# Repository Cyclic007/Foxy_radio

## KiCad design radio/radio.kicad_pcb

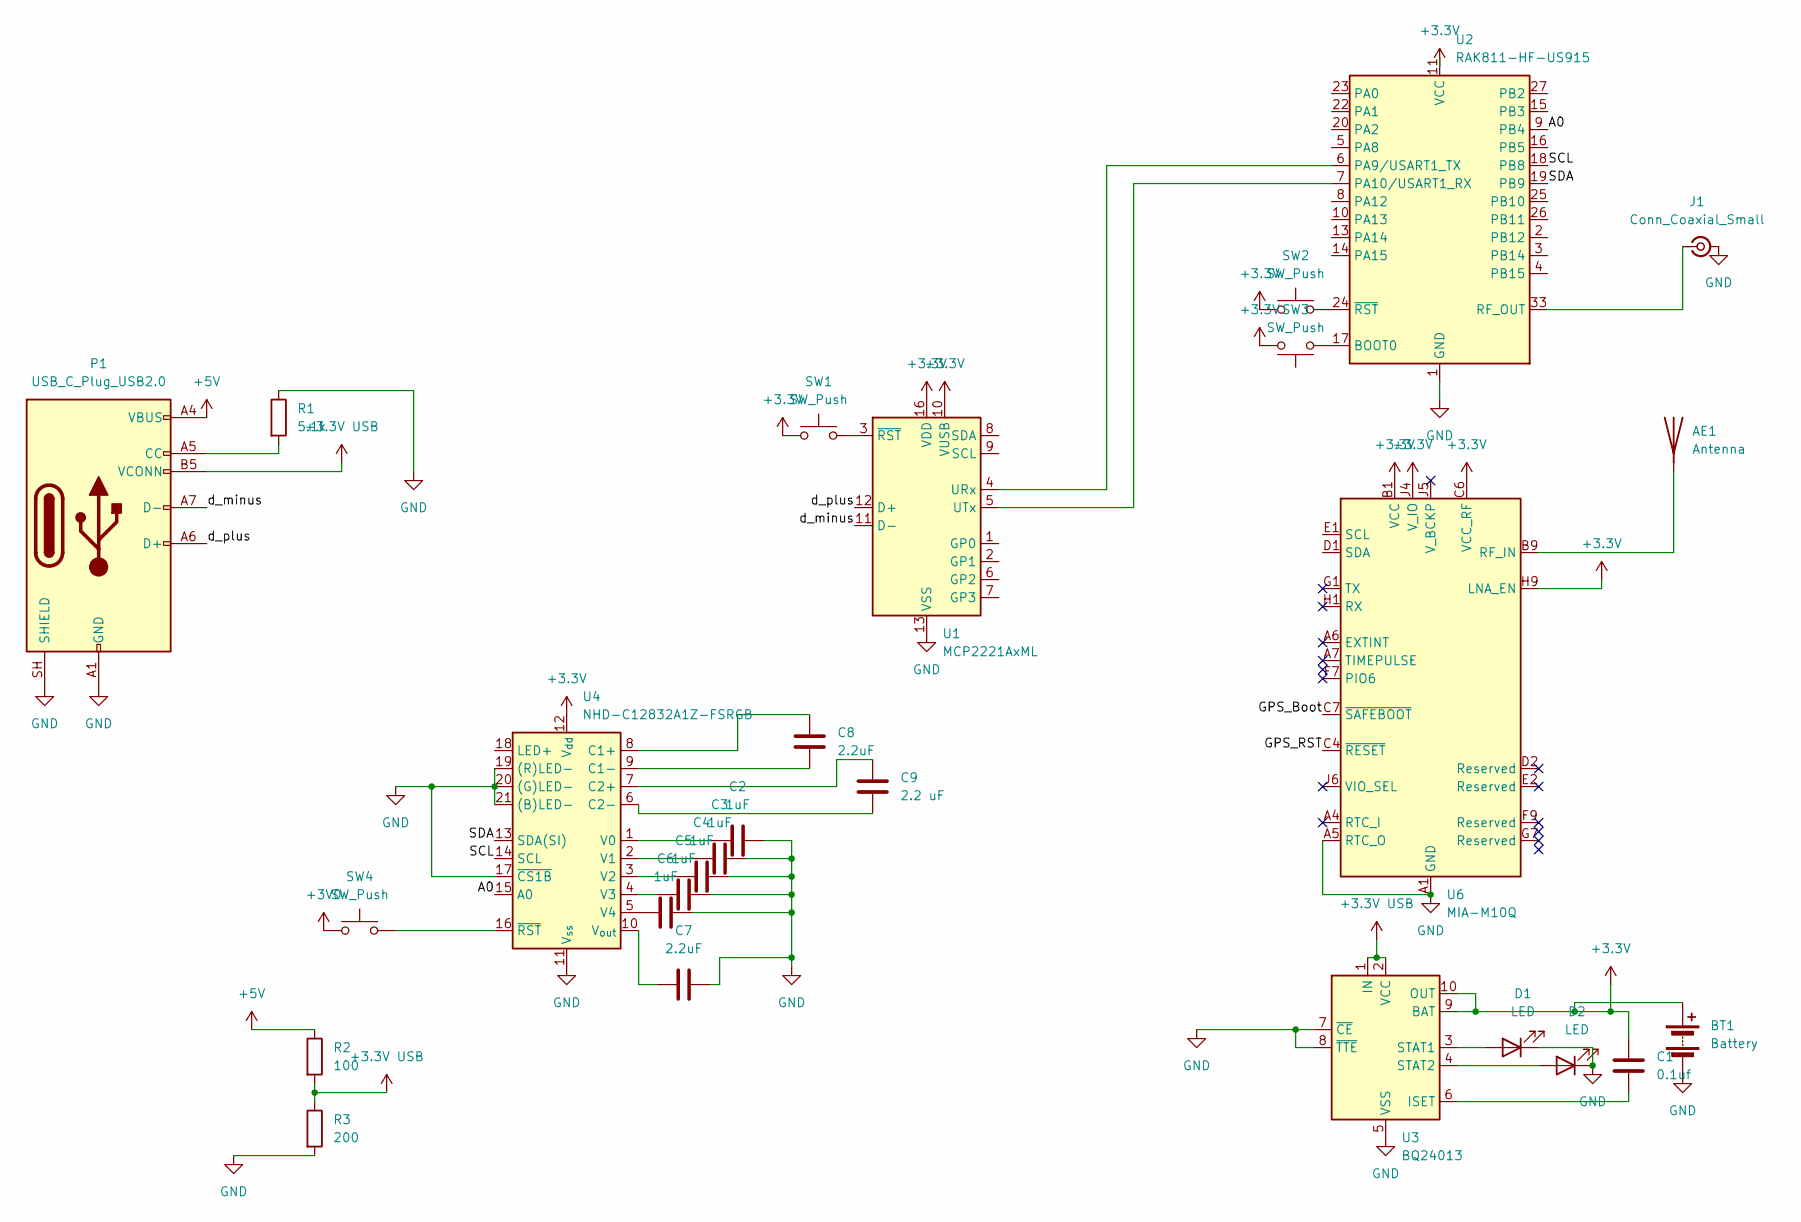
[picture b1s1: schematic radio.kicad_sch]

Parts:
AE1: Antenna; ANT_GP.1575.18.4.A.02_TAL
BT1: Battery; JST_XH_S2B-XH-A_1x02_P2.50mm_Horizontal
C1: 0.1uf; C_1812_4532Metric
C2, C3, C4, C5, C6: 1uF; C_1206_3216Metric
C7, C8: 2.2uF; C_1206_3216Metric
C9: 2.2 uF; C_1206_3216Metric
D1, D2: LED; LED_01005_0402Metric_Pad0.57x0.30mm_HandSolder
J1: Conn_Coaxial_Small; SMA_Amphenol_132291_Vertical
P1: USB_C_Plug_USB2.0; USB_C_Receptacle_Amphenol_124019772112A
R1: 5.1k; R_1225_3264Metric
R2: 100; R_1225_3264Metric
R3: 200; R_1225_3264Metric
SW1, SW2, SW3, SW4: SW_Push; SW_Push_SPST_NO_Alps_SKRK
U1: MCP2221AxML; QFN-16-1EP_4x4mm_P0.65mm_EP2.5x2.5mm
U2: RAK811-HF-US915; RAK811
U3: BQ24013; Texas_DRC0010J_ThermalVias
U4: NHD-C12832A1Z-FSRGB
U6: MIA-M10Q; ublox_LGA-53_4.5x4.5mm_Layout9x9_P0.5mm

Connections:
+3.3V: BT1.1 (+), C1.1, SW1.1, SW2.1, SW3.2, U1.10 (VUSB), U1.16 (VDD), U2.11 (VCC), U3.9 (BAT), U3.10 (OUT), U4.12 (V_{dd}), U6.B1 (VCC), U6.C6 (VCC_RF), U6.H9 (LNA_EN), U6.J4 (V_IO)
+3.3V USB: P1.B5 (VCONN), R2.2, R3.1, U3.1 (IN), U3.2 (VCC)
+3V0: SW4.1
+5V: P1.A4 (VBUS), P1.A9 (VBUS), P1.B4 (VBUS), P1.B9 (VBUS), R2.1
/A0: U2.9 (PB4), U4.15 (A0)
/GPS_Boot: U6.C7 (~SAFEBOOT)
/GPS_RST: U6.C4 (~RESET)
/SCL: U2.18 (PB8), U4.14 (SCL)
/SDA: U2.19 (PB9), U4.13 (SDA(SI))
/d_minus: P1.A7 (D-), U1.11 (D-)
/d_plus: P1.A6 (D+), U1.12 (D+)
GND: BT1.2 (-), C2.1, C3.2, C4.1, C5.1, C6.2, C7.2, D1.1 (K), D2.1 (K), J1.2 (Ext), P1.A1 (GND), P1.A12 (GND), P1.B1 (GND), P1.B12 (GND), P1.SH (SHIELD), R1.1, R3.2, U1.13 (VSS), U2.1 (GND), U2.12 (GND), U2.21 (GND), U2.28 (GND), U2.29 (GND), U2.30 (GND), U2.31 (GND), U2.32 (GND), U2.34 (GND), U3.5 (VSS), U3.7 (~CE), U3.8 (~TTE), U3.11 (VSS), U4.11 (V_{ss}), U4.17 (~CS1B), U4.19 ((R)LED-), U4.20 ((G)LED-), U4.21 ((B)LED-), U6.A1 (GND), U6.A2 (GND), U6.A3 (GND), U6.A5 (RTC_O), U6.A8 (GND), U6.A9 (GND), U6.B2 (GND), U6.B8 (GND), U6.C3 (GND), U6.C9 (GND), U6.E3 (GND), U6.E4 (GND), U6.E9 (GND), U6.F1 (GND), U6.F3 (GND), U6.F4 (GND), U6.G3 (GND), U6.G4 (GND), U6.G5 (GND), U6.G6 (GND), U6.H8 (GND), U6.J8 (GND), U6.J9 (GND)
unnamed: AE1.1 (A_1), U6.B9 (RF_IN)
unnamed: D1.2 (A), U3.3 (STAT1)
unnamed: D2.2 (A), U3.4 (STAT2)
unnamed: J1.1 (In), U2.33 (RF_OUT)
unnamed: P1.A5 (CC), R1.2
unnamed: U1.4 (URx), U2.6 (PA9/USART1_TX)
unnamed: U1.5 (UTx), U2.7 (PA10/USART1_RX)
unnamed: SW1.2, U1.3 (~RST)
unnamed: SW3.1, U2.17 (BOOT0)
unnamed: SW2.2, U2.24 (~RST)
unnamed: C1.2, U3.6 (ISET)
unnamed: C8.1, U4.8 (C1+)
unnamed: C8.2, U4.9 (C1-)
unnamed: C9.1, U4.7 (C2+)
unnamed: C9.2, U4.6 (C2-)
unnamed: C2.2, U4.1 (V0)
unnamed: C3.1, U4.2 (V1)
unnamed: C4.2, U4.3 (V2)
unnamed: C5.2, U4.4 (V3)
unnamed: C6.1, U4.5 (V4)
unnamed: C7.1, U4.10 (V_{out})
unnamed: SW4.2, U4.16 (~RST)

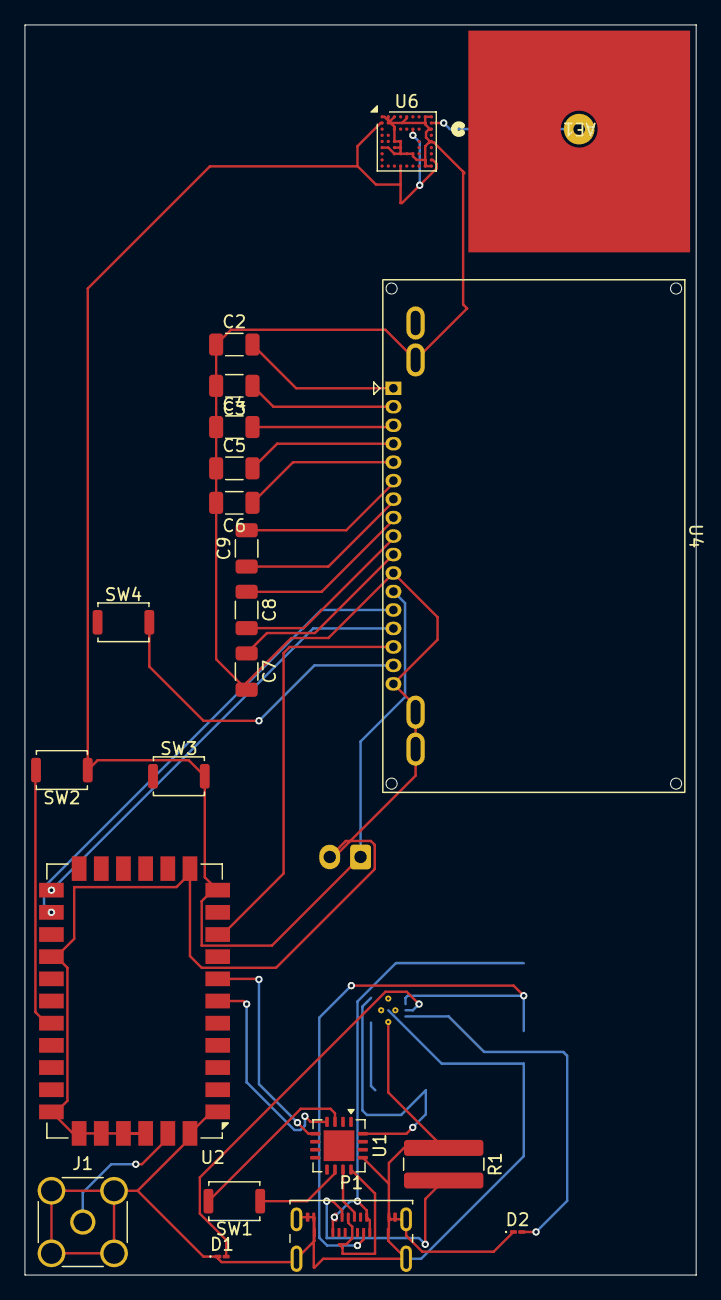
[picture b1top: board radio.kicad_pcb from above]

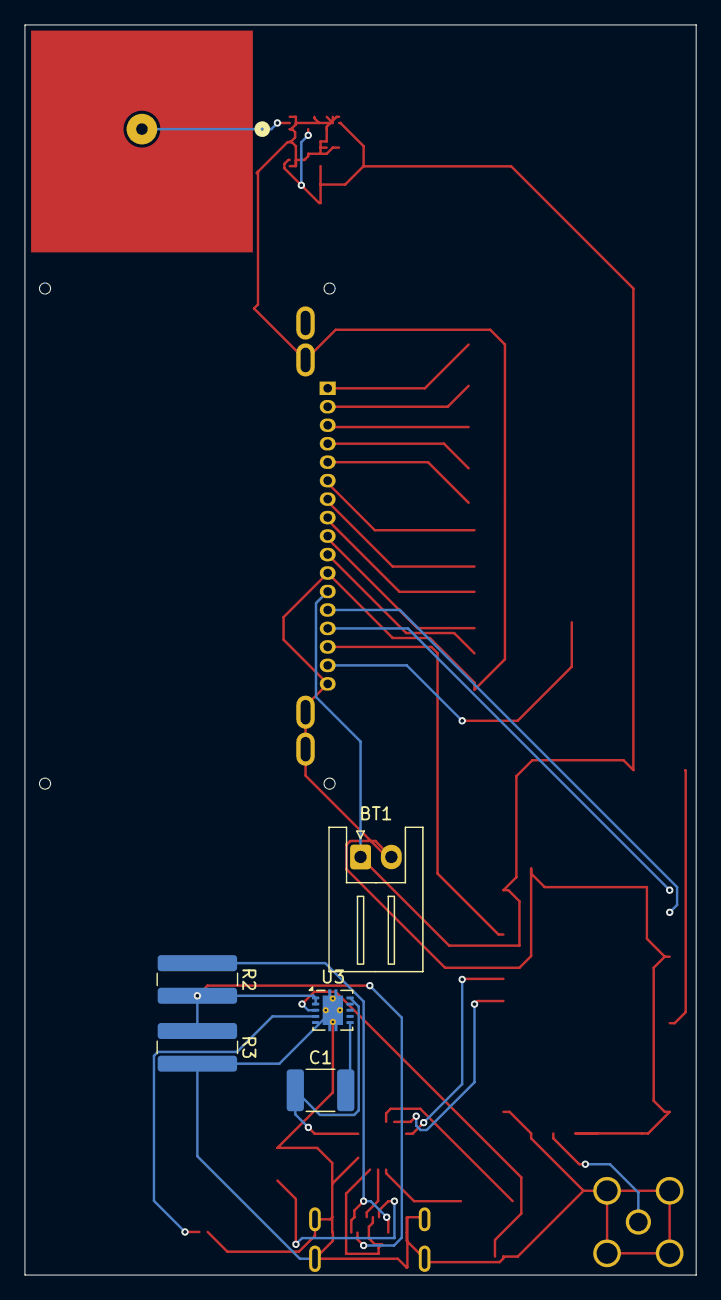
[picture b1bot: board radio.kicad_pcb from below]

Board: 2 copper layers, 54.5 x 101.5 mm, 27 parts (5 on the bottom side), 31 nets.

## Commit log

2026-05-04 start
2026-05-04 jornal
